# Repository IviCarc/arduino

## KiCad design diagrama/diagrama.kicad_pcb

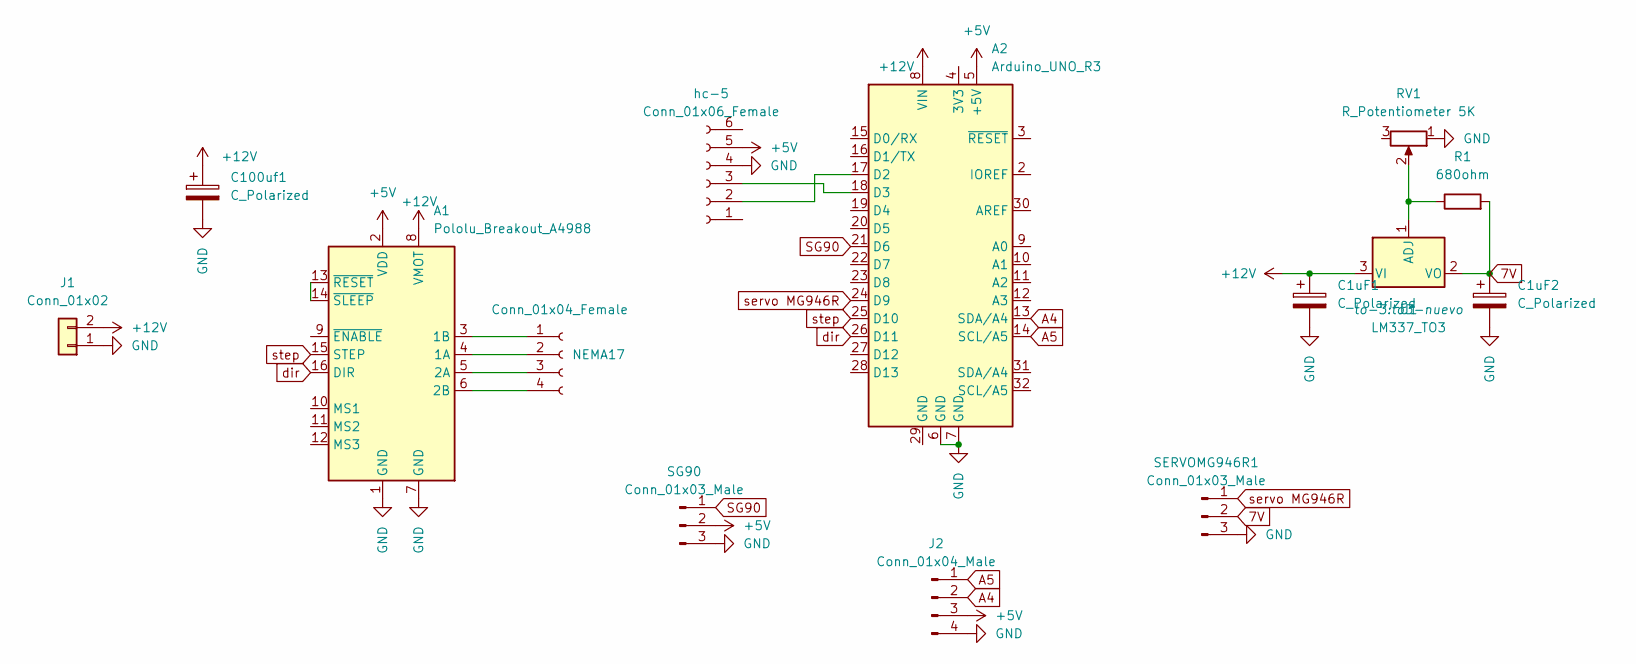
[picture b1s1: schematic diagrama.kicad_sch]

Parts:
A1: Pololu_Breakout_A4988; Pololu_Breakout-16_15.2x20.3mm
A2: Arduino_UNO_R3; Arduino_UNO_R3_WithMountingHoles
C1uF1, C1uF2, C100uf1: C_Polarized; C_Radial_D6.3mm_H11.0mm_P2.50mm
J1: Conn_01x02; TerminalBlock_Altech_AK300-2_P5.00mm
J2: Conn_01x04_Male; PinHeader_1x04_P2.54mm_Vertical
NEMA17: Conn_01x04_Female; TerminalBlock_Altech_AK300-4_P5.00mm
R1: 680ohm; R_Axial_DIN0207_L6.3mm_D2.5mm_P10.16mm_Horizontal
RV1: R_Potentiometer 5K; Potentiometer_Bourns_3296W_Vertical
SERVOMG946R1: Conn_01x03_Male; PinHeader_1x03_P2.54mm_Vertical
SG90: Conn_01x03_Male; PinHeader_1x03_P2.54mm_Vertical
U1: LM337_TO3; to3-nuevo
hc-5: Conn_01x06_Female; PinSocket_1x06_P2.54mm_Vertical

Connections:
7V: C1uF2.1, R1.2, SERVOMG946R1.2, U1.2 (VO)
+5V: A1.2 (VDD), A2.5 (+5V), J2.3, SG90.2, hc-5.5
+12V: A1.8 (VMOT), A2.8 (VIN), C1uF1.1, C100uf1.1, J1.2, U1.3 (VI)
A4: A2.13 (SDA/A4), J2.2
A5: A2.14 (SCL/A5), J2.1
GND: A1.1 (GND), A1.7 (GND), A2.6 (GND), A2.7 (GND), C1uF1.2, C1uF2.2, C100uf1.2, J1.1, J2.4, RV1.1, SERVOMG946R1.3, SG90.3, hc-5.4
unnamed: A1.4 (1A), NEMA17.2
unnamed: A1.3 (1B), NEMA17.1
unnamed: A1.5 (2A), NEMA17.3
unnamed: A1.6 (2B), NEMA17.4
unnamed: A1.13 (~RESET), A1.14 (~SLEEP)
unnamed: A2.17 (D2), hc-5.2
unnamed: A2.18 (D3), hc-5.3
unnamed: R1.1, RV1.2, U1.1 (ADJ)
SG90: A2.21 (D6), SG90.1
dir: A1.16 (DIR), A2.26 (D11)
servo MG946R: A2.24 (D9), SERVOMG946R1.1
step: A1.15 (STEP), A2.25 (D10)

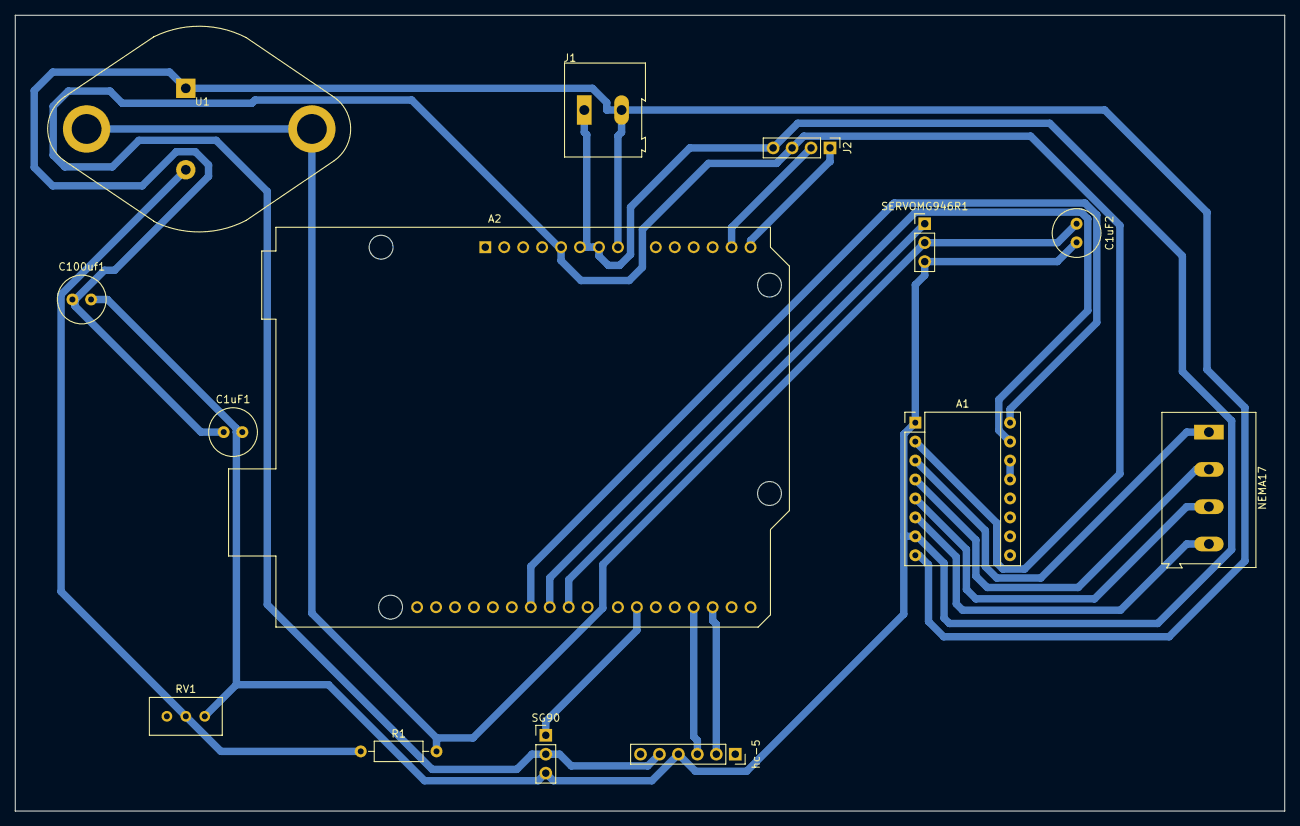
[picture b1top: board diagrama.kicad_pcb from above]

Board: 2 copper layers, 170.2 x 106.7 mm, 14 parts (0 on the bottom side), 18 nets.

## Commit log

2022-05-28 first
2022-05-28 motor integrado con app finalizado y servo test
2022-05-31 Cambio toFloat
    Cambio de toInt a toFloat
2022-05-31 adicion motor
2022-05-31 calibracion motor em
2022-06-02 Implementacion Servo MG946R
2022-06-02 intento lcd con motor
2022-06-05 .vscode
2022-06-16 Corte con ServoMotor
2022-06-28 Caracteristicas motores
2022-06-29 calculo circunferencia
2022-07-26 CALIBRACION EJE NEMA
2022-09-22 diagramas y cambio de pines por la plaqueta
2022-10-06 diagrama rehecho
2022-10-11 eliminado input del ancho y muestra del progreso y cm en el lcd
2022-10-13 to3 de lado correcto
2022-10-24 calibrado servo mg49 tanto en angulo como en delay
2022-10-24 mejor documentacion del codigo
2022-10-24 nuevo test para el pelado y corte del cable
2022-10-24 nuevo test para la comunicacion bluetooth
2022-10-25 Integración de los tres códigos y desconexión bluetooth en la app
2022-10-25 Revert "Integración de los tres códigos y desconexión bluetooth en la app"
    This reverts commit 9461b82b90ef126367f21ecf8f04b96c3e268ba1.
2022-10-28 calibracion motor
2022-11-01 agregado tercer input y corregido error con los decimales
2022-11-03 cambio de libreria del servo y velocidad del nema
2022-11-17 calibrado el pelado
2022-11-29 agregado sevo.detach y bajada velocidad del paso a paso
2023-10-19 agregado nuevo encapsulado al to3 y circuito terminado
2023-11-22 agregado cuarto input
